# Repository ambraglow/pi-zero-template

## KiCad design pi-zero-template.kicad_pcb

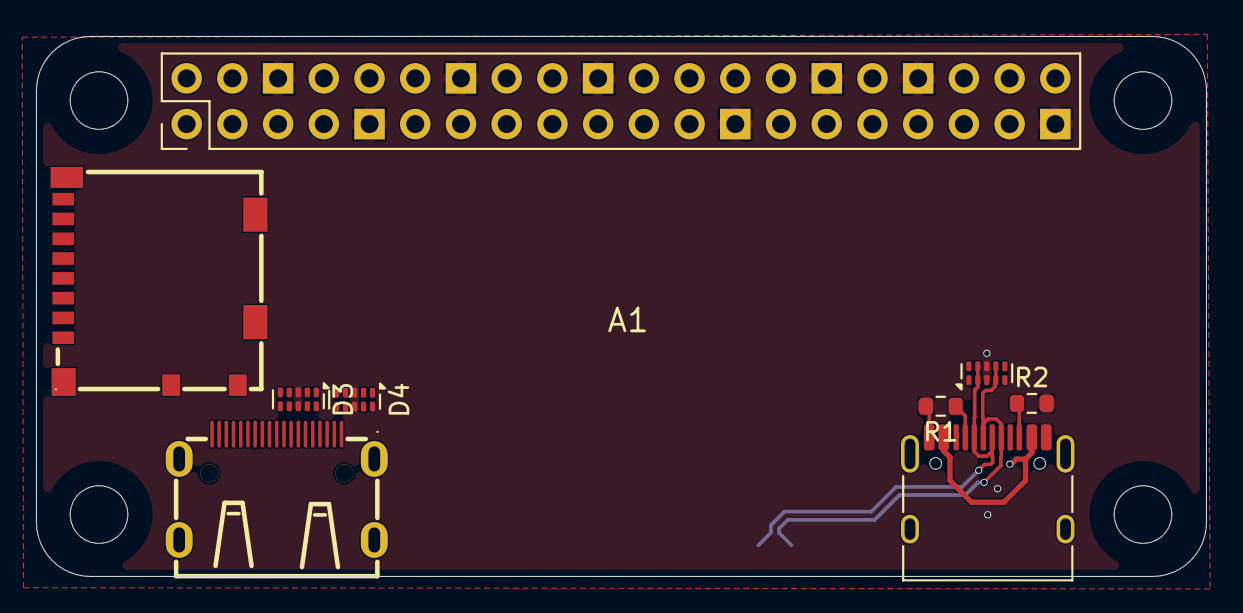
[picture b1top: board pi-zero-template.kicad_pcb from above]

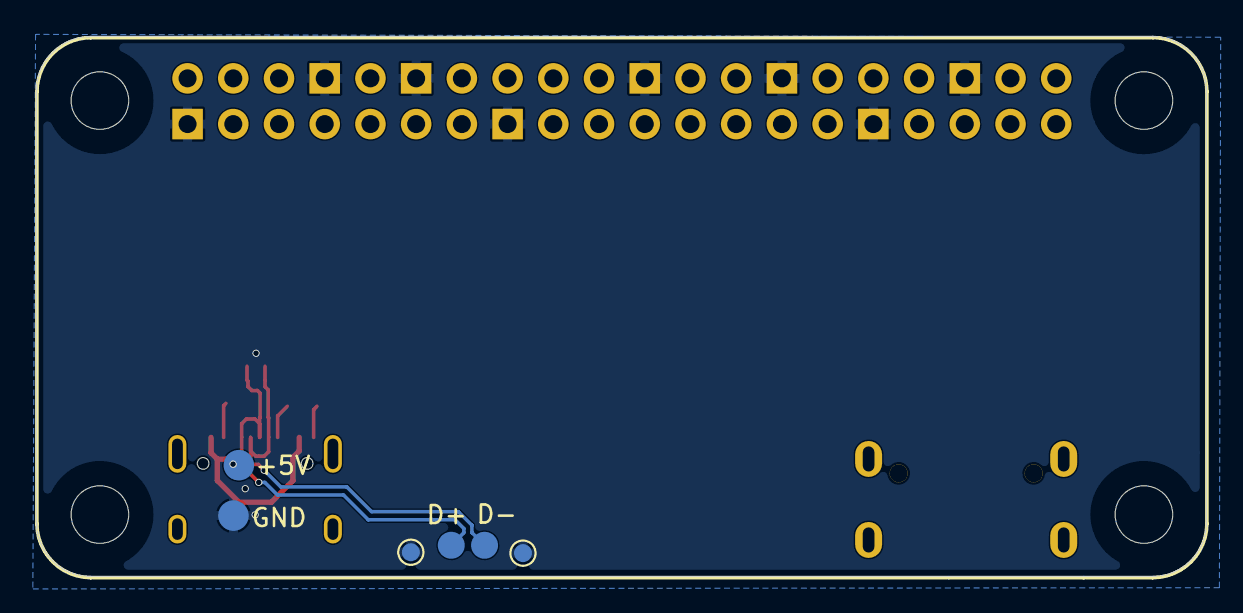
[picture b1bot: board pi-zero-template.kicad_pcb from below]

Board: 2 copper layers, 65.0 x 30.0 mm, 11 parts (2 on the bottom side), 21 nets.

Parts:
A1: Raspberry Pi Zero Headers; RASPI_ZERO_FULL
D1, D3, D4: TPAZ1043-04F; USON-10_2.5x1.0mm_P0.5mm
J1: HDMI_C_1.3; HDMI-SMD_19P-P0.40-H-F_HDMI-519
J2: USB_C_Receptacle; USB_C_Receptacle_HRO_TYPE-C-31-M-12
R1, R2: 5.1k; R_0603_1608Metric
SIM1: 1040310811; SIM-SMD_8P-1040310811
TP3, TP4: TestPoint; TestPoint_Pad_D1.0mm

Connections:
/HDMI_CK+: D3.4 (IO3), D3.7 (NC), J1.11 (CK+)
/HDMI_CK-: D3.5 (IO4), D3.6 (NC), J1.12 (CK-)
/HDMI_D0+: D3.1 (IO1), D3.10 (NC), J1.8 (D0+)
/HDMI_D0-: D3.2 (IO2), D3.9 (NC), J1.9 (D0-)
/HDMI_D1+: D4.4 (IO3), D4.7 (NC), J1.5 (D1+)
/HDMI_D1-: D4.5 (IO4), D4.6 (NC), J1.6 (D1-)
/HDMI_D2+: D4.1 (IO1), D4.10 (NC), J1.2 (D2+)
/HDMI_D2-: D4.2 (IO2), D4.9 (NC), J1.3 (D2-)
/SD_CLK: A1.15 (GP22/SD_CLK), SIM1.5 (CLK)
/SD_CMD: A1.16 (GP23/SD_CMD), SIM1.3 (CMD)
/SD_DAT0: A1.18 (GP24/SD_D0), SIM1.7 (DAT0)
/SD_DAT1: A1.22 (GP25/SD_D1), SIM1.8 (DAT1)
/SD_DAT2: A1.37 (GP26/SD_D2), SIM1.1 (DAT2)
/USB_D+: A1.PP22 (USB_D+), D1.4 (IO3), D1.7 (NC), J2.A6 (D+), J2.B6 (D+)
/USB_D-: A1.PP23 (USB_D-), D1.2 (IO2), D1.9 (NC), J2.A7 (D-), J2.B7 (D-)
GND: A1.6 (GND), A1.9 (GND), A1.14 (GND), A1.20 (GND), A1.25 (GND), A1.30 (GND), A1.34 (GND), A1.39 (GND), A1.PP6 (GND), D1.3 (G), D1.8 (G), D3.3 (G), D3.8 (G), D4.3 (G), D4.8 (G), J1.13 (GND), J2.A1 (GND), J2.A12 (GND), J2.B1 (GND), J2.B12 (GND), R1.2, R2.2, TP3.1 (1_1), TP4.1 (1_1)
unnamed: D1.1 (IO1), D1.10 (NC)
unnamed: D1.5 (IO4), D1.6 (NC)
unnamed: J2.A5 (CC1), R1.1
unnamed: J2.B5 (CC2), R2.1
VBUS_USB: A1.2 (+5V), A1.4 (+5V), A1.PP1 (+5V_USB), J1.18 (+5V), J2.A4 (VBUS), J2.A9 (VBUS), J2.B4 (VBUS), J2.B9 (VBUS)
